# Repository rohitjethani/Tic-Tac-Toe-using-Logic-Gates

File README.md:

# Tic-Tac-Toe-using-Logic-Gates

There have been many software implementations of Tic-Tac-Toe.
There have been a few hardware implementations on breadboard but none of them is where it was converted to PCB (Printed Circuit Board).
For this project, I am using KiCAD software. It is a open source software. I did an online course on Udemy 'Introduction to KiCAD' by Javier Martinez.

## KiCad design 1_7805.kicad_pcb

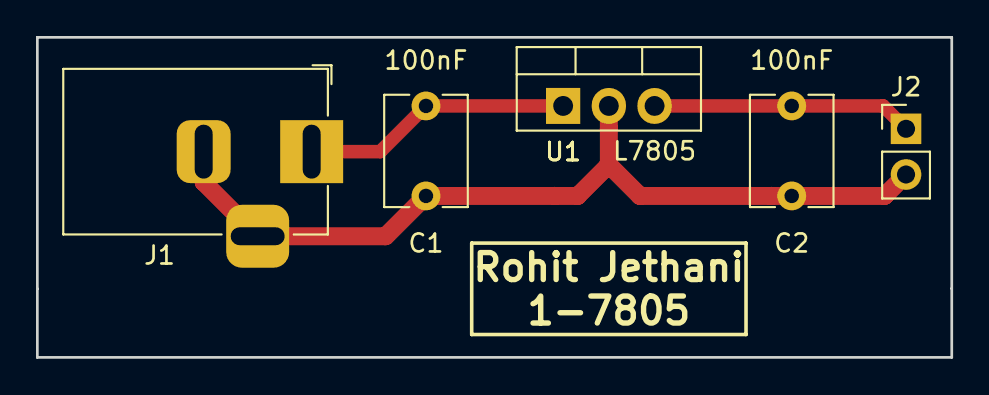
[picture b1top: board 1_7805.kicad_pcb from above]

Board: 2 copper layers, 50.8 x 17.8 mm, 5 parts (0 on the bottom side), 3 nets.

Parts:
C1, C2: 100nF; C_Disc_D6.0mm_W4.4mm_P5.00mm
J1: Jack-DC; BarrelJack_Horizontal
J2: Conn_01x02; PinHeader_1x02_P2.54mm_Vertical
U1: L7805; TO-220-3_Vertical

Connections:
GND: C1.2, C2.2, J1.2, J1.3, J2.2, U1.2
unnamed: C1.1, J1.1, U1.1
unnamed: C2.1, J2.1, U1.3

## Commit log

2019-10-13 Uploading additional files
